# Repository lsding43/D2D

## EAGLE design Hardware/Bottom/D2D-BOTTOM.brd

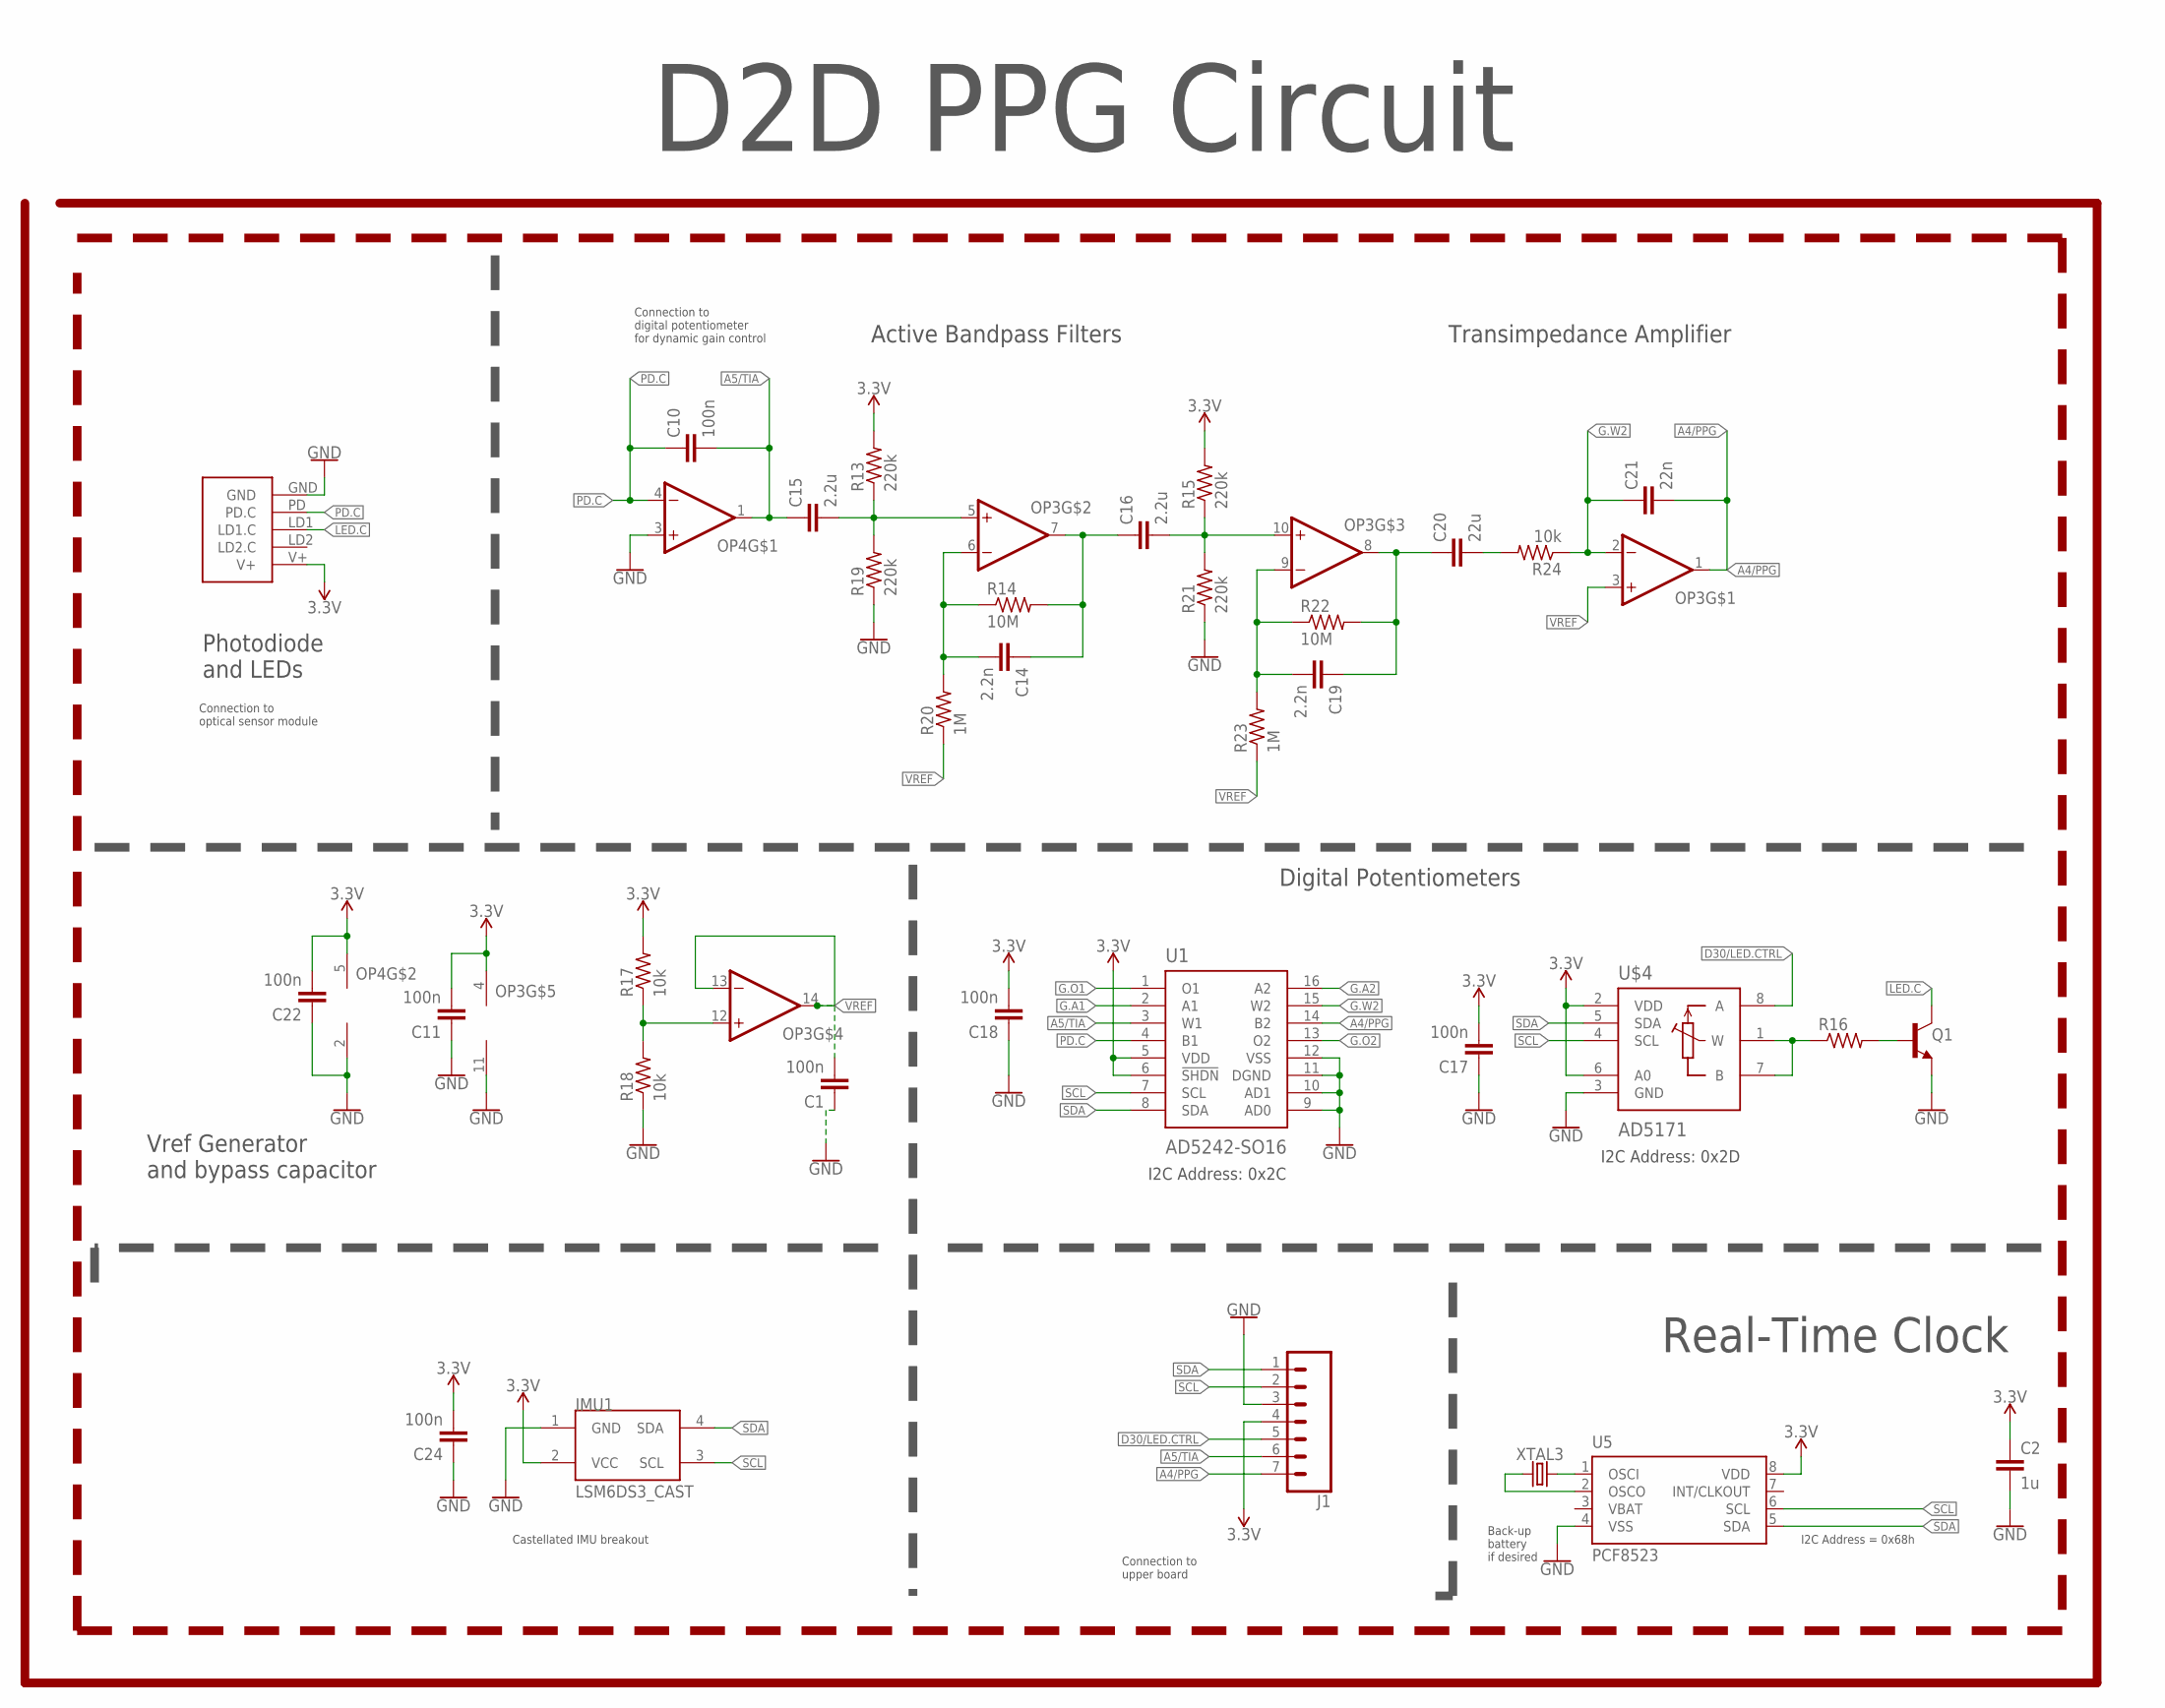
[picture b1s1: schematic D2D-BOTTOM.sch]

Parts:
C1, C10, C11, C17, C18, C22, C24: 100n; C0603
C2: 1u; C0603
C14, C19: 2.2n; C0603
C15, C16: 2.2u; C0603
C20: 22u; C0603
C21: 22n; C0603
IMU1: LSM6DS3_CAST
J1: CONN_07-1.27MM; 1X07_1.27MM
OP3: OP-QUAD-SO14; SO14
OP4: OP-SINGLEOT; SOT23-5
Q1: NPN-GENERIC; SOT23-3
R13, R15, R19, R21: 220k; R0603
R14, R22: 10M; R0603
R16: RESISTOR0603; R0603
R17, R18: 10k; R0402
R20, R23: 1M; R0603
R24: 10k; R0603
U1: AD5242-SO16; SO16
U5: PCF8523; SO8; DIGIKEY 568-5306-1-ND
U$3: PPG.MODULE.2
U$4: AD5171; SOT-23-8
XTAL3: 32.7680kHz; 2-SMD.NOLEAD.2.0MMTO1.2MM

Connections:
3.3V: C2.1, C11.2, C17.2, C18.2, C22.2, C24.2, IMU1.2 (VCC), J1.4, OP3.4 (V+), OP4.5 (V+), R13.2, R15.2, R17.2, U1.5 (VDD), U1.6 (!SHDN), U5.8 (VDD), U$3.V+, U$4.2 (VDD), U$4.6 (A0)
A4/PPG: C21.2, J1.7, OP3.1 (OUT), U1.14 (B2)
A5/TIA: C10.2, C15.1, J1.6, OP4.1 (OUT), U1.3 (W1)
D30/LED.CTRL: J1.5, U$4.8 (A)
G.A1: U1.2 (A1)
G.A2: U1.16 (A2)
G.O1: U1.1 (O1)
G.O2: U1.13 (O2)
G.W2: C21.1, OP3.2 (-IN), R24.1, U1.15 (W2)
GND: C1.1, C2.2, C11.1, C17.1, C18.1, C22.1, C24.1, IMU1.1 (GND), J1.3, OP3.11 (V-), OP4.2 (V-), OP4.3 (+IN), Q1.2 (E), R18.1, R19.1, R21.1, U1.9 (AD0), U1.10 (AD1), U1.11 (DGND), U1.12 (VSS), U5.4 (VSS), U$3.GND, U$4.3 (GND)
LED.C: Q1.3 (C), U$3.LD1 (LD1.C)
unnamed: U5.2 (OSCO), XTAL3.P$1 (1)
unnamed: U5.1 (OSCI), XTAL3.P$2 (2)
unnamed: Q1.1 (B), R16.2
unnamed: R16.1, U$4.1 (W), U$4.7 (B)
unnamed: OP3.12 (+IN), R17.1, R18.2
unnamed: C15.2, OP3.5 (+IN), R13.1, R19.2
unnamed: C14.2, OP3.6 (-IN), R14.1, R20.2
unnamed: C14.1, C16.1, OP3.7 (OUT), R14.2
unnamed: C16.2, OP3.10 (+IN), R15.1, R21.2
unnamed: C19.2, OP3.9 (-IN), R22.1, R23.2
unnamed: C19.1, C20.1, OP3.8 (OUT), R22.2
unnamed: C20.2, R24.2
PD.C: C10.1, OP4.4 (-IN), U1.4 (B1), U$3.PD (PD.C)
SCL: IMU1.3 (SCL), J1.2, U1.7 (SCL), U5.6 (SCL), U$4.4 (SCL)
SDA: IMU1.4 (SDA), J1.1, U1.8 (SDA), U5.5 (SDA), U$4.5 (SDA)
VBAT: U5.3 (VBAT)
VREF: C1.2, OP3.3 (+IN), OP3.13 (-IN), OP3.14 (OUT), R20.1, R23.1

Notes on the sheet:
Photodiode and LEDs
Active Bandpass Filters
Digital Potentiometers
Transimpedance Amplifier
I2C Address: 0x2C
I2C Address: 0x2D
Connection to optical sensor module
Connection to digital potentiometer for dynamic gain control
Connection to upper board
Castellated IMU breakout
Vref Generator and bypass capacitor
D2D PPG Circuit
I2C Address = 0x68h
Back-up battery if desired
Real-Time Clock

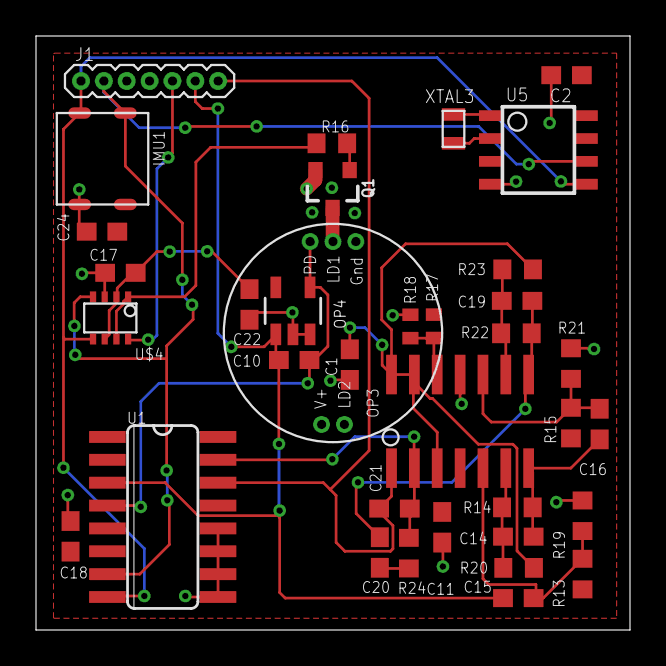
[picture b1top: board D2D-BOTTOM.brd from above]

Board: 2 copper layers, 33.0 x 33.0 mm, 36 parts (0 on the bottom side), 23 nets.

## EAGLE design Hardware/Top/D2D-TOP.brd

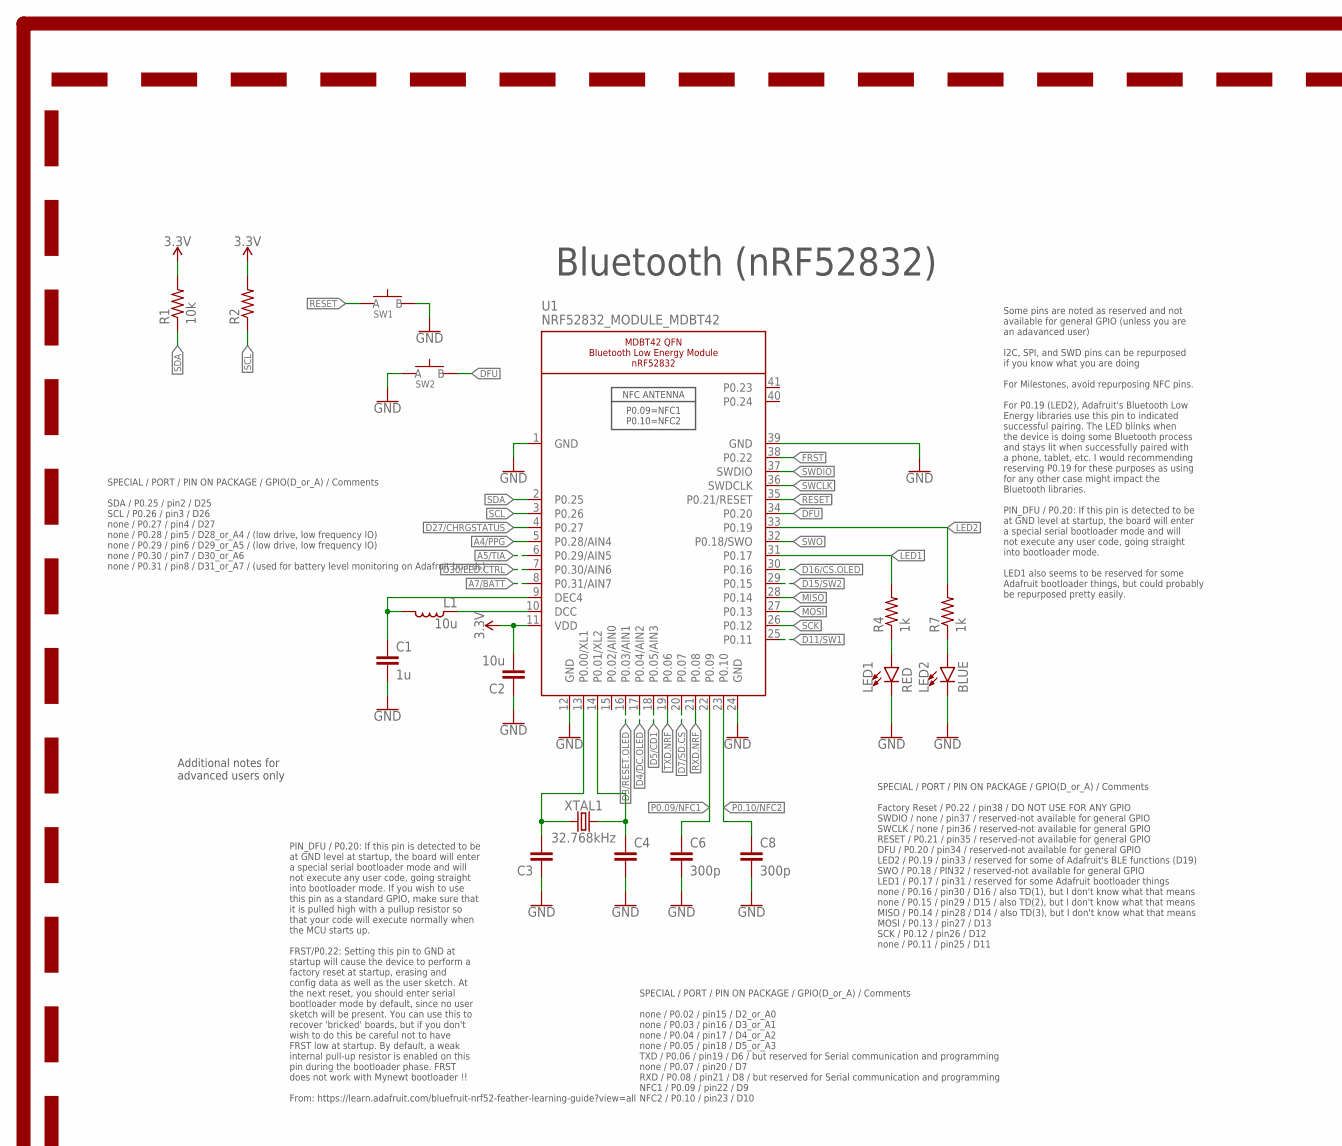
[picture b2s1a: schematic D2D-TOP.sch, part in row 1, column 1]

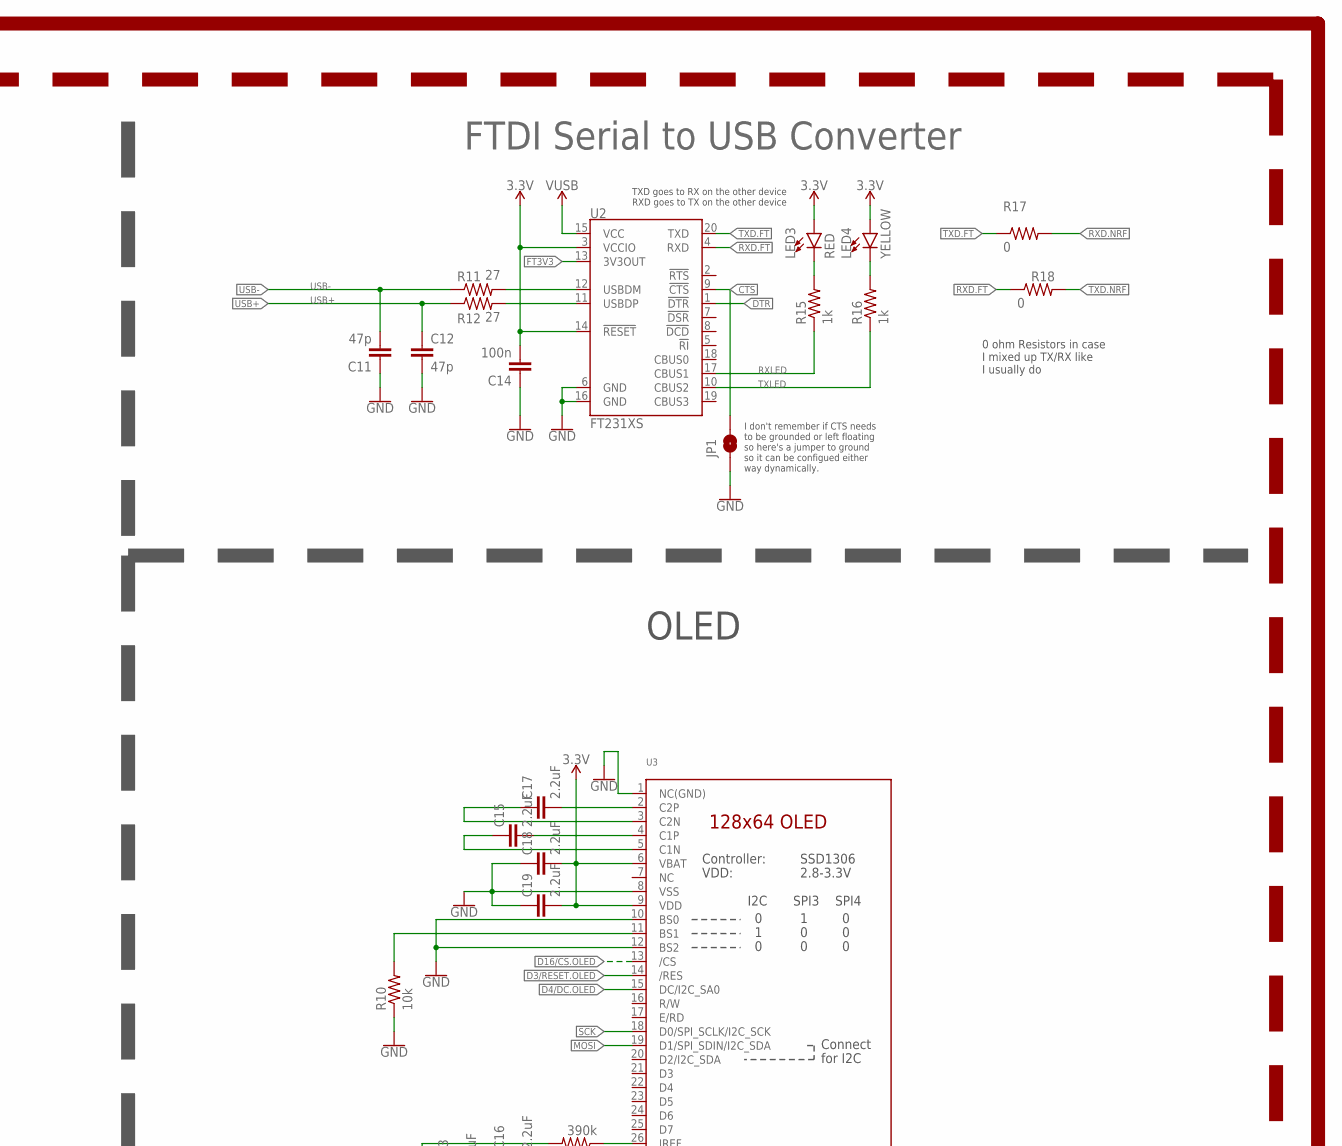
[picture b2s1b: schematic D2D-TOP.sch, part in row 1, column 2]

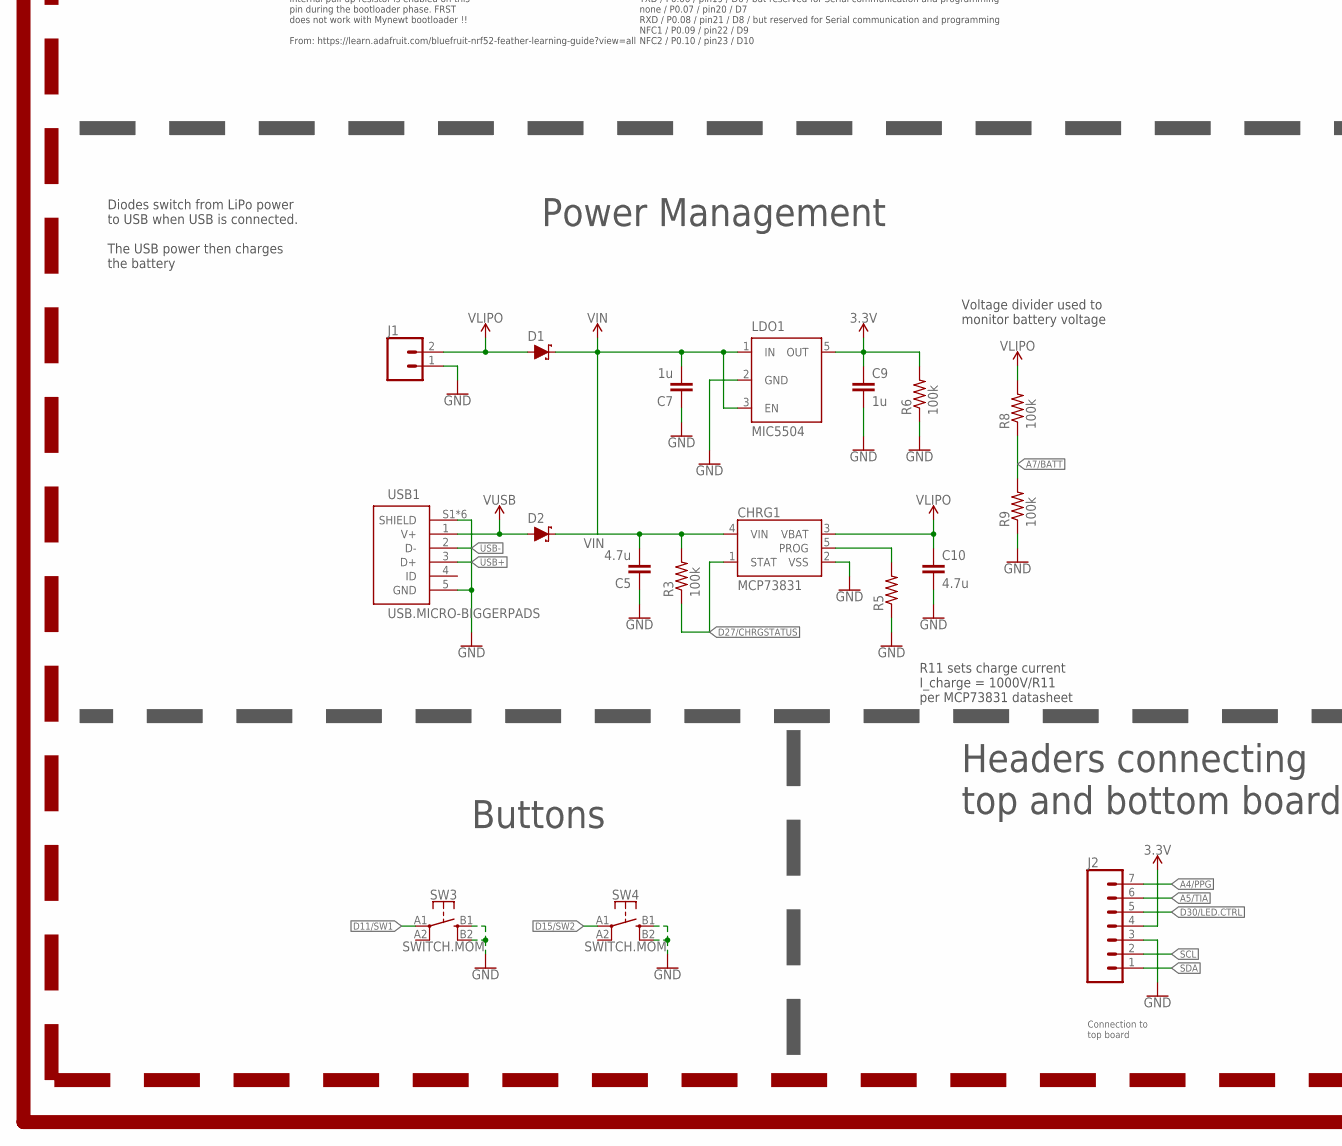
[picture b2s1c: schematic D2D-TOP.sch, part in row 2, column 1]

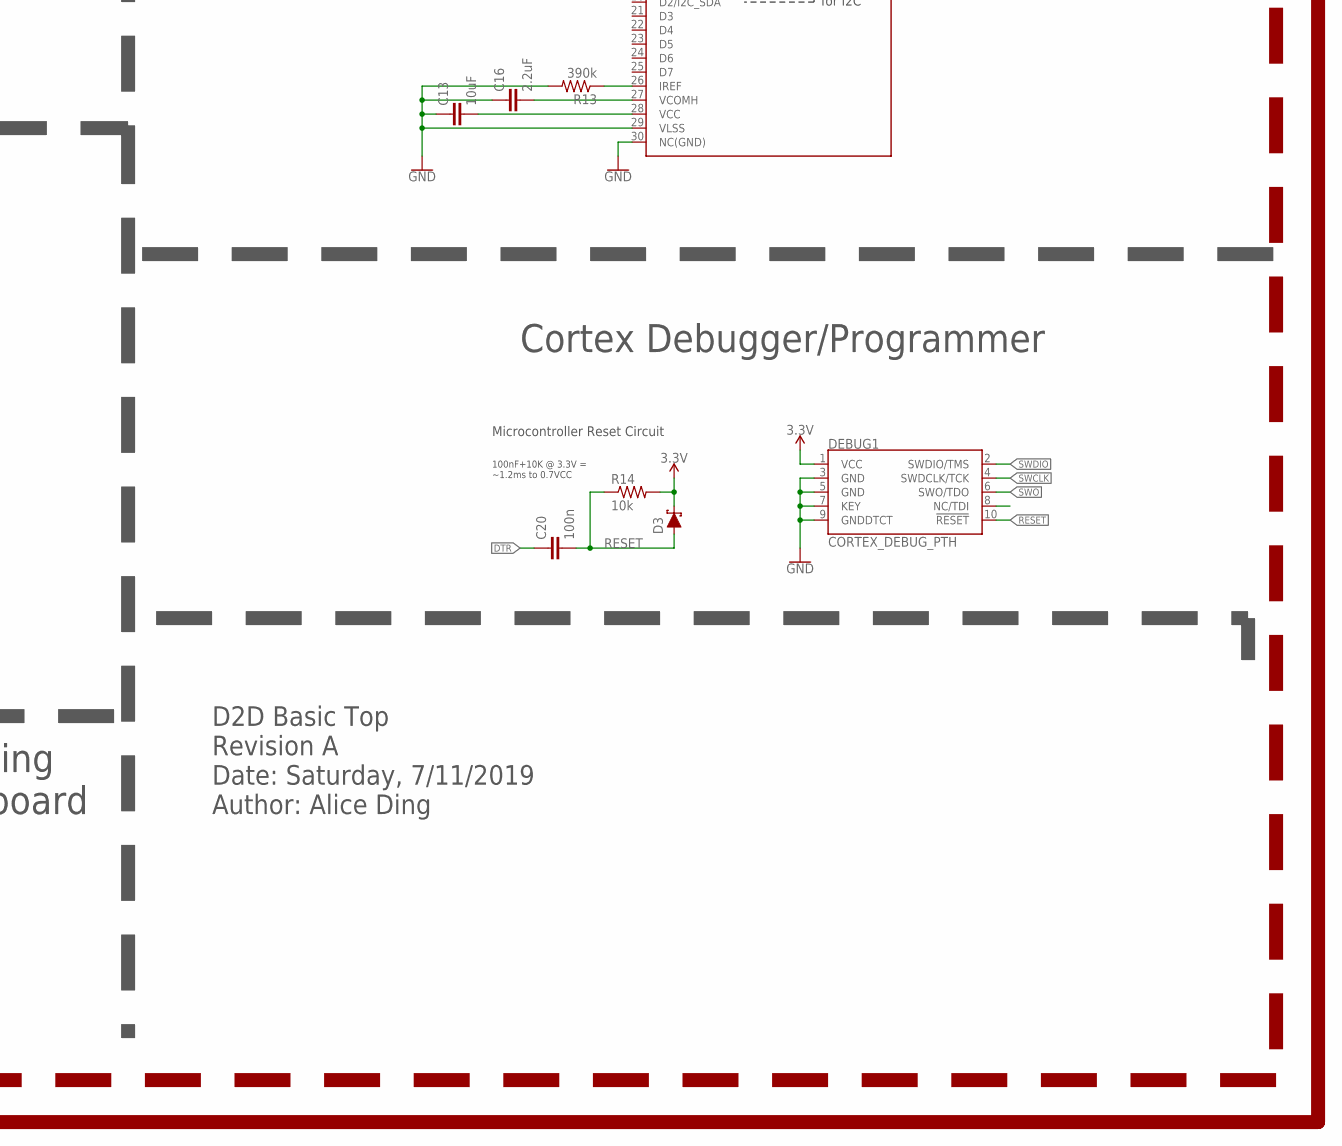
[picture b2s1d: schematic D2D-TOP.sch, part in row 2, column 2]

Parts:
C1, C7, C9: 1u; C0603
C2: 10u; C0805
C3, C4: CAPACITOR0603; C0603
C5, C10: 4.7u; C0603
C6, C8: 300p; C0603
C11, C12: 47p; C0603
C13: 10uF; C0603
C14, C20: 100n; C0603
C15, C16, C17, C18, C19: 2.2uF; C0402
CHRG1: MCP73831; SOT23-5
D1, D2, D3: SCHOTTKY-USC; USC
DEBUG1: CORTEX_DEBUG_PTH; 2X5-PTH-1.27MM
J1: CONN_02; 1X02
J2: CONN_07-1.27MM; 1X07_1.27MM
JP1: JUMPER-SMT_2_NO_SILK; SMT-JUMPER_2_NO_SILK
L1: 10u; L0603
LDO1: MIC5504; SOT23-5
LED1, LED3: RED; LED-0603
LED2: BLUE; LED-0603
LED4: YELLOW; LED-0603
R1, R10, R14: 10k; R0603
R2, R5: RESISTOR0603; R0603
R3, R6, R8, R9: 100k; R0603
R4, R7, R15, R16: 1k; R0603
R11, R12: 27; R0603
R13: 390k; R0603
R17, R18: 0; R0603
SW1, SW2: SPST-PTS830GG140-COPY.1-3; BUTTON-GULLWING
SW3, SW4: SWITCH.MOM; TACTILE_SWITCH_SMD_6.2MM_TALL
U1: NRF52832_MODULE_MDBT42; BLE_MODULE_RAYTAC_MDBT42
U2: FT231XS; SSOP20_L
U3: DISP_OLED_UG-2864HSWEG01-NO-WRAPAROUND; UG-2864HSWEG01_0.96IN_NO-WRAPAROUND
USB1: USB.MICRO-BIGGERPADS; USB-MICRO-01.BIGGERPADS
XTAL1: 32.768kHz; 2-SMD.NOLEAD.2.0MMTO1.2MM

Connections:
3.3V: C2.2, C9.1, C14.2, C18.2, C19.2, D3.- (C), DEBUG1.1 (VCC), J2.4, LDO1.5 (OUT), LED3.A, LED4.A, R1.2, R2.2, R6.2, R14.2, U1.11 (VDD), U2.3 (VCCIO), U2.14 (!RESET), U3.6 (VBAT), U3.9 (VDD)
A4/PPG: J2.7, U1.5 (P0.28/AIN4)
A5/TIA: J2.6, U1.6 (P0.29/AIN5)
A7/BATT: R8.1, R9.2, U1.8 (P0.31/AIN7)
CTS: JP1.2, U2.9 (!CTS)
D3/RESET.OLED: U1.16 (P0.03/AIN1), U3.14 (/RES)
D4/DC.OLED: U1.17 (P0.04/AIN2), U3.15 (DC/I2C_SA0)
D5/CD1: U1.18 (P0.05/AIN3)
D7/SD.CS: U1.20 (P0.07)
D11/SW1: SW3.A1 (1), U1.25 (P0.11)
D15/SW2: SW4.A1 (1), U1.29 (P0.15)
D16/CS.OLED: U1.30 (P0.16), U3.13 (/CS)
D27/CHRGSTATUS: CHRG1.1 (STAT), R3.1, U1.4 (P0.27)
D30/LED.CTRL: J2.5, U1.7 (P0.30/AIN6)
DFU: SW2.3 (B), U1.34 (P0.20)
DTR: C20.1, U2.1 (!DTR)
FRST: U1.38 (P0.22)
FT3V3: U2.13 (3V3OUT)
GND: C1.2, C2.1, C3.1, C4.2, C5.1, C6.2, C7.1, C8.2, C9.2, C10.2, C11.1, C12.2, C13.1, C14.1, C16.1, C18.1, C19.1, CHRG1.2 (VSS), DEBUG1.3 (GND), DEBUG1.5 (GND), DEBUG1.7 (KEY), DEBUG1.9 (GNDDTCT), J1.1, J2.3, JP1.1, LDO1.2 (GND), LED1.C, LED2.C, R5.1, R6.1, R9.1, R10.1, R13.2, SW1.3 (B), SW2.1 (A), SW3.B1 (3), SW3.B2 (4), SW4.B1 (3), SW4.B2 (4), U1.1 (GND), U1.12 (GND), U1.24 (GND), U1.39 (GND), U2.6 (GND), U2.16 (GND), U3.1 (NC(GND)), U3.8 (VSS), U3.10 (BS0), U3.12 (BS2), U3.29 (VLSS), U3.30 (NC(GND)), USB1.5 (GND), USB1.S1 (SHIELD), USB1.S2 (SHIELD), USB1.S3 (SHIELD), USB1.S4 (SHIELD), USB1.S5 (SHIELD), USB1.S6 (SHIELD)
LED1: R4.2, U1.31 (P0.17)
LED2: R7.2, U1.33 (P0.19)
MISO: U1.28 (P0.14)
MOSI: U1.27 (P0.13), U3.19 (D1/SPI_SDIN/I2C_SDA)
unnamed: R10.2, U3.11 (BS1)
unnamed: R13.1, U3.26 (IREF)
unnamed: C17.2, U3.2 (C2P)
unnamed: C3.2, U1.13 (P0.00/XL1), XTAL1.P$1 (1)
unnamed: C17.1, U3.3 (C2N)
unnamed: C4.1, U1.14 (P0.01/XL2), XTAL1.P$2 (2)
unnamed: C15.2, U3.4 (C1P)
unnamed: C15.1, U3.5 (C1N)
unnamed: LED1.A, R4.1
unnamed: LED2.A, R7.1
unnamed: L1.1, U1.10 (DCC)
unnamed: C1.1, L1.2, U1.9 (DEC4)
unnamed: C13.2, U3.28 (VCC)
unnamed: C16.2, U3.27 (VCOMH)
unnamed: CHRG1.5 (PROG), R5.2
unnamed: R11.2, U2.12 (USBDM)
unnamed: R12.2, U2.11 (USBDP)
unnamed: LED3.C, R15.2
unnamed: LED4.C, R16.2
P0.09/NFC1: C6.1, U1.22 (P0.09)
P0.10/NFC2: C8.1, U1.23 (P0.10)
RESET: C20.2, D3.+ (A), DEBUG1.10 (!RESET), R14.1, SW1.1 (A), U1.35 (P0.21/RESET)
RXD.FT: R18.1, U2.4 (RXD)
RXD.NRF: R17.2, U1.21 (P0.08)
RXLED: R15.1, U2.17 (CBUS1)
SCK: U1.26 (P0.12), U3.18 (D0/SPI_SCLK/I2C_SCK)
SCL: J2.2, R2.1, U1.3 (P0.26)
SDA: J2.1, R1.1, U1.2 (P0.25)
SWCLK: DEBUG1.4 (SWDCLK/TCK), U1.36 (SWDCLK)
SWDIO: DEBUG1.2 (SWDIO/TMS), U1.37 (SWDIO)
SWO: DEBUG1.6 (SWO/TDO), U1.32 (P0.18/SWO)
TXD.FT: R17.1, U2.20 (TXD)
TXD.NRF: R18.2, U1.19 (P0.06)
TXLED: R16.1, U2.10 (CBUS2)
USB+: C12.1, R12.1, USB1.3 (D+)
USB-: C11.2, R11.1, USB1.2 (D-)
VIN: C5.2, C7.2, CHRG1.4 (VIN), D1.- (C), D2.- (C), LDO1.1 (IN), LDO1.3 (EN), R3.2
VLIPO: C10.1, CHRG1.3 (VBAT), D1.+ (A), J1.2, R8.2
V_USB: D2.+ (A), U2.15 (VCC), USB1.1 (V+)

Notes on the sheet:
Microcontroller Reset Circuit
100nF+10K @ 3.3V = ~1.2ms to 0.7VCC
SPECIAL / PORT / PIN ON PACKAGE / GPIO(D_or_A) / Comments SDA / P0.25 / pin2 / D25 SCL / P0.26 / pin3 / D26 none / P0.27 / pin4 / D27 none / P0.28 / pin5 / D28_or_A4 / (low drive, low frequency IO) none / P0.29 / pin6 / D29_or_A5 / (low drive, low frequency IO) none / P0.30 / pin7 / D30_or_A6 none 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
SPECIAL / PORT / PIN ON PACKAGE / GPIO(D_or_A) / Comments none / P0.02 / pin15 / D2_or_A0 none / P0.03 / pin16 / D3_or_A1 none / P0.04 / pin17 / D4_or_A2 none / P0.05 / pin18 / D5_or_A3 TXD / P0.06 / pin19 / D6 / but reserved for Serial communication and programming none / P0.07 / pin20 / D7 RXD / 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
SPECIAL / PORT / PIN ON PACKAGE / GPIO(D_or_A) / Comments Factory Reset / P0.22 / pin38 / DO NOT USE FOR ANY GPIO SWDIO / none / pin37 / reserved-not available for general GPIO SWCLK / none / pin36 / reserved-not available for general GPIO RESET / P0.21 / pin35 / reserved-not available for general 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
Some pins are noted as reserved and not available for general GPIO (unless you are an adavanced user) I2C, SPI, and SWD pins can be repurposed if you know what you are doing For Milestones, avoid repurposing NFC pins. For P0.19 (LED2), Adafruit's Bluetooth Low Energy libraries use this pin to indic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
PIN_DFU / P0.20: If this pin is detected to be at GND level at startup, the board will enter a special serial bootloader mode and will not execute any user code, going straight into bootloader mode. If you wish to use this pin as a standard GPIO, make sure that it is pulled high with a pullup resis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
Additional notes for advanced users only
Bluetooth (nRF52832)
OLED
Power Management
Buttons
Cortex Debugger/Programmer
TXD goes to RX on the other device RXD goes to TX on the other device
I don't remember if CTS needs to be grounded or left floating so here's a jumper to ground so it can be configued either way dynamically.
FTDI Serial to USB Converter
Connection to top board
D2D Basic Top Revision A Date: Saturday, 7/11/2019 Author: Alice Ding
Diodes switch from LiPo power to USB when USB is connected. The USB power then charges the battery
R11 sets charge current I_charge = 1000V/R11 per MCP73831 datasheet
Voltage divider used to monitor battery voltage
Headers connecting top and bottom board
0 ohm Resistors in case I mixed up TX/RX like I usually do

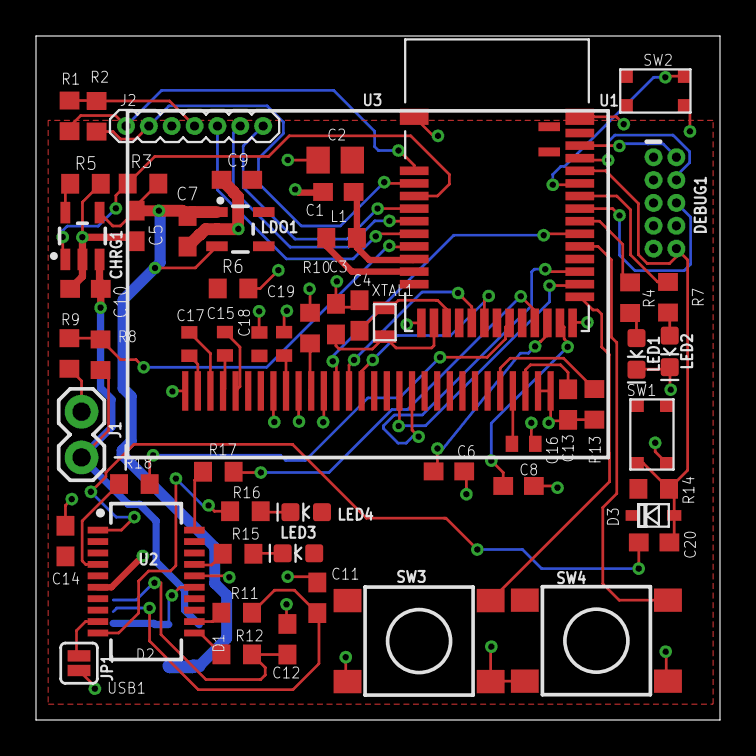
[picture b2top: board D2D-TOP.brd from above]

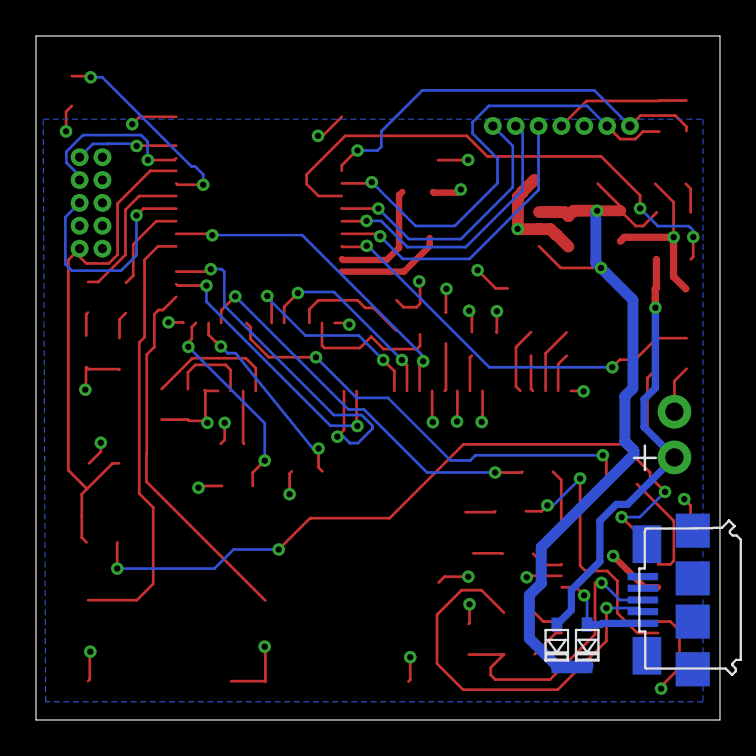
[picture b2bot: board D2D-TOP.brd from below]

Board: 2 copper layers, 38.0 x 38.0 mm, 61 parts (3 on the bottom side), 57 nets.

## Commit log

2020-05-28 features list
2020-06-04 added D2D.docx
2020-06-04 organized repository
2020-06-04 top schematic
2020-06-11 current top and bottom board
2020-06-12 unfinished 002
2020-06-17 updated to 002
2020-06-18 checkpoint 3
2020-06-24 added starting code
2020-06-24 updated top board
2020-06-29 completed 004
2020-07-02 fixed error
2020-07-02 push onto repo
2020-07-02 finished 006
2020-07-08 Finish Top
2020-07-11 Finished Top board with modifications
2020-07-12 fixed up top schematic
2020-07-14 finished bottom board
